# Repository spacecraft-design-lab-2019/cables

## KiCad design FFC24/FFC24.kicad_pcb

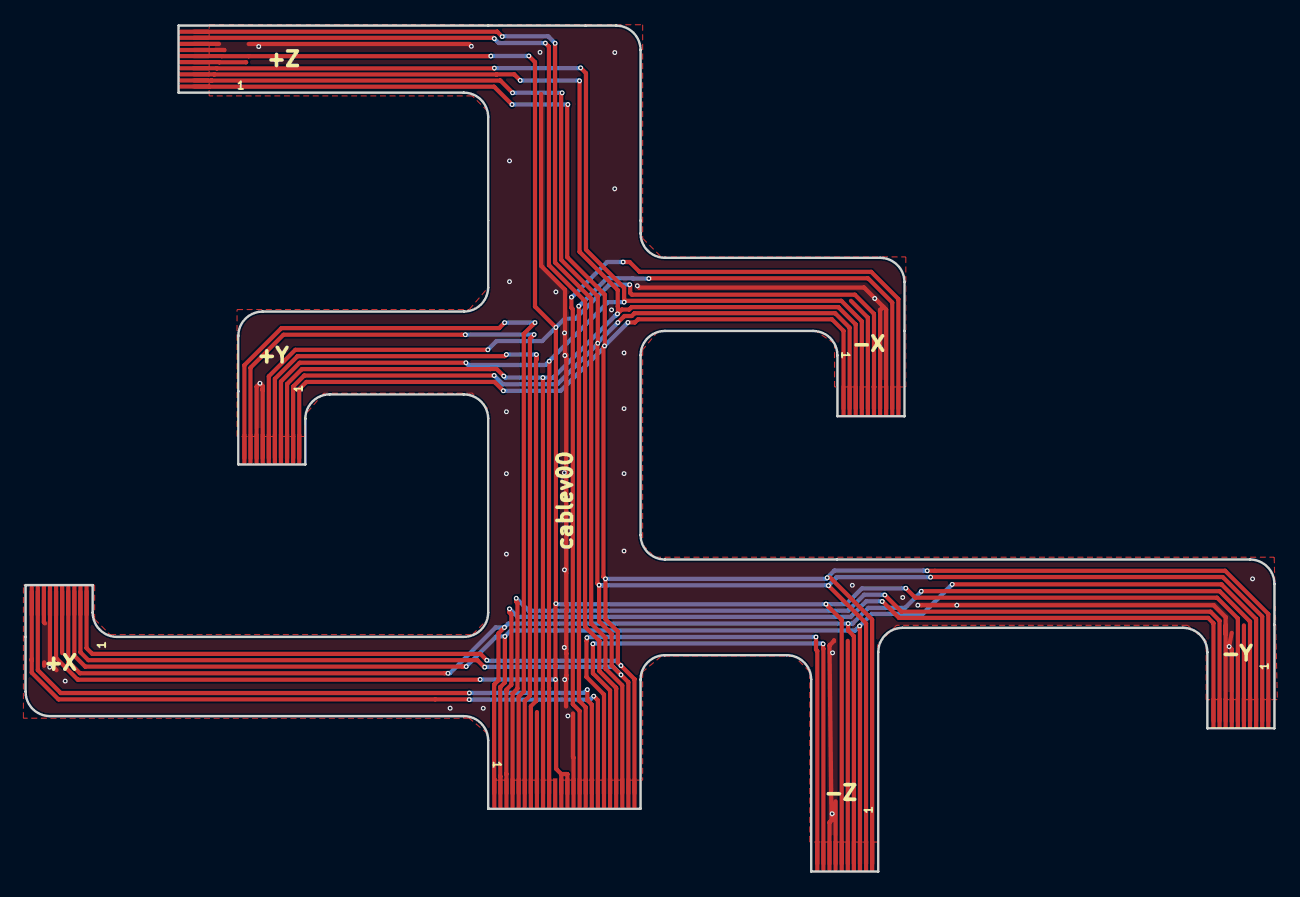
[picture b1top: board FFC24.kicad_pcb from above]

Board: 2 copper layers, 102.5 x 69.4 mm, 7 parts (0 on the bottom side), 21 nets.

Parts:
J1, J2, J4, J5, J6, J7: XF2M-1015-1A-mod; FFC-10pin
J3: xf2m-2415-1a-mod; FFC-24pin

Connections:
3V3: J1.6, J2.6, J3.12, J3.13, J4.6, J5.6, J6.6, J7.6
BATT_N: J1.2, J2.2, J3.23, J4.2, J5.2, J6.2, J7.2
BATT_P: J1.1, J2.1, J3.24, J4.1, J5.1, J6.1, J7.1
BURN1: J3.7, J6.5
COIL1_N: J3.21, J7.9
COIL1_P: J3.22, J7.10
COIL2_N: J1.9, J3.20
COIL2_P: J1.10, J3.19
COIL3_N: J3.17, J5.9
COIL3_P: J3.18, J5.10
COIL4_N: J3.16, J4.9
COIL4_P: J3.15, J4.10
COIL5_N: J3.6, J6.9
COIL5_P: J3.5, J6.10
COIL6_N: J2.9, J3.4
COIL6_P: J2.10, J3.3
GND: J1.7, J1.8, J2.7, J2.8, J3.14, J4.7, J4.8, J5.7, J5.8, J6.7, J6.8, J7.7, J7.8
SCL1: J3.10, J4.4, J6.4, J7.4
SCL2: J1.4, J2.4, J3.1, J5.4
SDA1: J3.9, J4.3, J6.3, J7.3
SDA2: J1.3, J2.3, J3.2, J5.3

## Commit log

2019-10-30 roughing out FFC schematic
2019-10-30 FWIW
2019-11-01 pinout
2019-11-05 added example routing scheme. see #115 for discussion
2019-11-17 DXF export from Fusion 360. V7
2019-11-18 cleaning up schematic paths
2019-12-02 changed dimensions to fit spec
2019-12-03 starting to route flex cable
2019-12-04 roughed out the layout
2019-12-04 FFC tweaks
2019-12-06 FFC clean up
2019-12-06 first cable order
2020-02-04 generated schematic PDF
2020-02-19 v2 for fabrication
2020-02-19 corrupt file
